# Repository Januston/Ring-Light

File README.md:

# Ring-Light
🤖 Showcasing our PCB ring light for the 2019 FRC competition! 💡 A blend of innovation and precision, it illuminated our robot's journey. 🏆 A proud testament to engineering finesse in FRC robotics. 🛠️ Celebrate creativity and dedication with us! 🎉

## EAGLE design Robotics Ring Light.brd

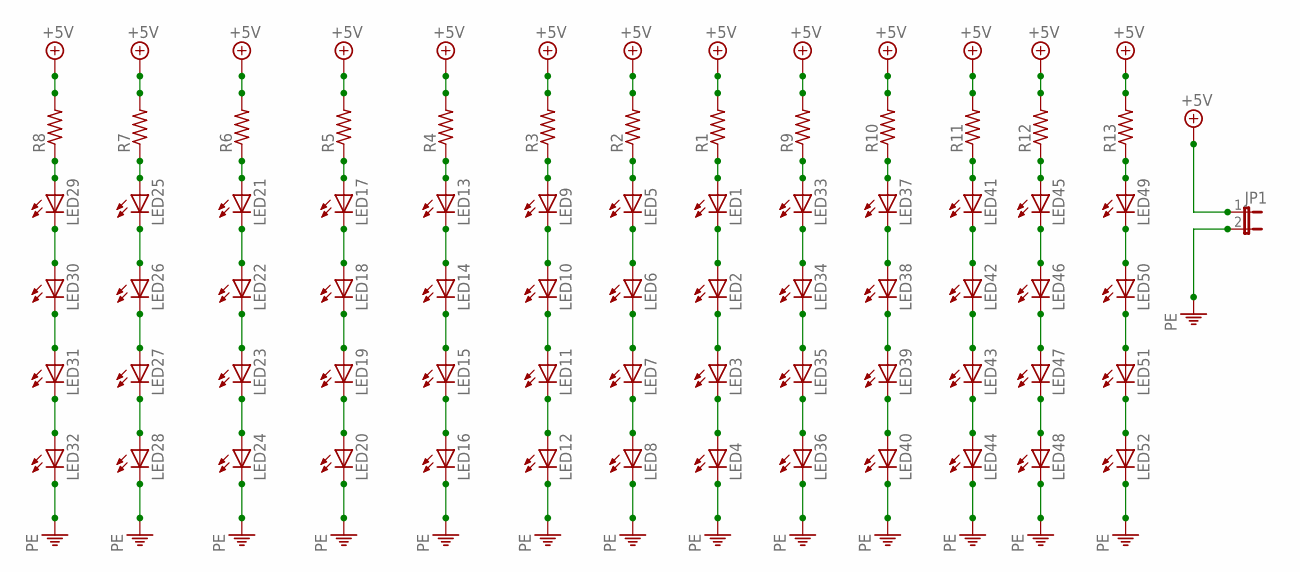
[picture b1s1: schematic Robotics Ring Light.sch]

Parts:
JP1: JP1E; JP1
LED1, LED2, LED3, LED4, LED5, LED6, LED7, LED8, LED9, LED10, LED11, LED12, LED13, LED14, LED15, LED16, LED17, LED18, LED19, LED20, LED21, LED22, LED23, LED24, LED25, LED26, LED27, LED28, LED29, LED30, LED31, LED32, LED33, LED34, LED35, LED36, LED37, LED38, LED39, LED40, LED41, LED42, LED43, LED44, LED45, LED46, LED47, LED48, LED49, LED50, LED51, LED52: LED5MM
R1, R2, R3, R4, R5, R6, R7, R8, R9, R10, R11, R12, R13: R-US_0207/10; 0207/10

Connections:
+5V: JP1.1, R1.2, R2.2, R3.2, R4.2, R5.2, R6.2, R7.2, R8.2, R9.2, R10.2, R11.2, R12.2, R13.2
unnamed: LED1.K (C), LED2.A
unnamed: LED2.K (C), LED3.A
unnamed: LED3.K (C), LED4.A
unnamed: LED5.K (C), LED6.A
unnamed: LED1.A, R1.1
unnamed: LED6.K (C), LED7.A
unnamed: LED7.K (C), LED8.A
unnamed: LED5.A, R2.1
unnamed: LED9.K (C), LED10.A
unnamed: LED10.K (C), LED11.A
unnamed: LED11.K (C), LED12.A
unnamed: LED9.A, R3.1
unnamed: LED13.K (C), LED14.A
unnamed: LED14.K (C), LED15.A
unnamed: LED15.K (C), LED16.A
unnamed: LED13.A, R4.1
unnamed: LED17.K (C), LED18.A
unnamed: LED18.K (C), LED19.A
unnamed: LED19.K (C), LED20.A
unnamed: LED17.A, R5.1
unnamed: LED21.K (C), LED22.A
unnamed: LED22.K (C), LED23.A
unnamed: LED23.K (C), LED24.A
unnamed: LED21.A, R6.1
unnamed: LED25.K (C), LED26.A
unnamed: LED26.K (C), LED27.A
unnamed: LED27.K (C), LED28.A
unnamed: LED25.A, R7.1
unnamed: LED29.K (C), LED30.A
unnamed: LED30.K (C), LED31.A
unnamed: LED31.K (C), LED32.A
unnamed: LED29.A, R8.1
unnamed: LED33.K (C), LED34.A
unnamed: LED34.K (C), LED35.A
unnamed: LED35.K (C), LED36.A
unnamed: LED33.A, R9.1
unnamed: LED37.K (C), LED38.A
unnamed: LED38.K (C), LED39.A
unnamed: LED39.K (C), LED40.A
unnamed: LED37.A, R10.1
unnamed: LED41.K (C), LED42.A
unnamed: LED42.K (C), LED43.A
unnamed: LED43.K (C), LED44.A
unnamed: LED41.A, R11.1
unnamed: LED45.K (C), LED46.A
unnamed: LED46.K (C), LED47.A
unnamed: LED47.K (C), LED48.A
unnamed: LED45.A, R12.1
unnamed: LED49.K (C), LED50.A
unnamed: LED50.K (C), LED51.A
unnamed: LED51.K (C), LED52.A
unnamed: LED49.A, R13.1
PE: JP1.2, LED4.K (C), LED8.K (C), LED12.K (C), LED16.K (C), LED20.K (C), LED24.K (C), LED28.K (C), LED32.K (C), LED36.K (C), LED40.K (C), LED44.K (C), LED48.K (C), LED52.K (C)

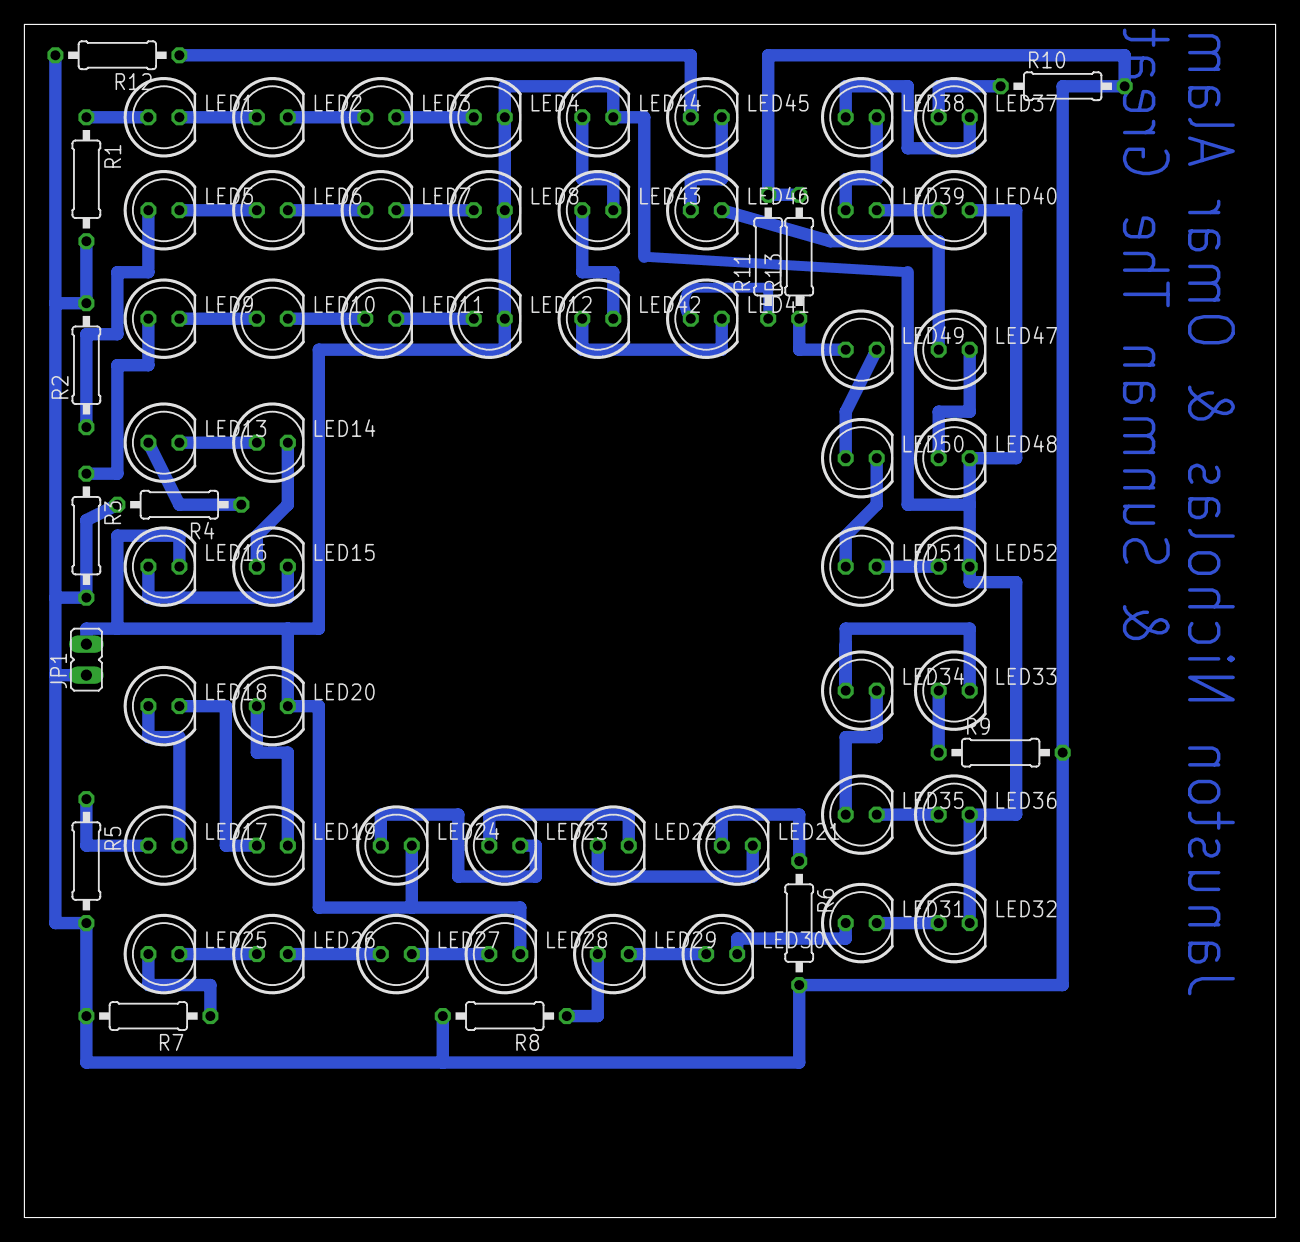
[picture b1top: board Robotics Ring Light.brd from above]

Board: 2 copper layers, 102.5 x 97.8 mm, 66 parts (0 on the bottom side), 54 nets.

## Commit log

2023-09-23 add files
